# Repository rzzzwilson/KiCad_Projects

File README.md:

# KiCad_Projects
A place for my KiCad designs.

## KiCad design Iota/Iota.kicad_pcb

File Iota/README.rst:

What is this?
=============

*Iota* is a minimal arduino-like clone of the
`Teensy 2.0 <https://www.pjrc.com/store/teensy.html>`_.
It is designed to be pin compatible with the Teensy without some of its features,
particularly:

* 5Volt circuit only
* mostly the same pinout as the Teensy

The aim is to not just get a working Teensy 2 clone, but to ensure that my
knowledge of how to build something like a Teensy is adequate.  Later the
Iota design will be embedded in designs such as the Headless VFO, a version
of DigitalVFO without the display and rotary encoder.

Design Documents
----------------

The *Misc* directory contains various documents:

* teensy_2.gif - the Teensy 2 schematic
* Teensy_2.0_pinout.png - the Teensy 2 pinout

The design of the *Iota* will start with the teensy_2.gif schematic.

Status
------

The 1.0 version was a bust.  The micro USB SMD mount components I ordered don't
match the component footprint I used on the PCB.  There's no way to bodge the
SMD components to fit the board, so onto version 1.1.

2019_04_03: The 1.1 board using an SMD mini B USB socket has arrived.  After
fiddling with the crystal loading capacitors (increased to 22pF) and burning a
bootloader into the CPU, IT WORKS!   Here's a picture of it running the Adafruit
GFX library demo using an little 128x64 OLED display from AliExpress:

.. image:: IMG_5709.JPG

Burning the bootloader
----------------------

I followed this procedure to
`bootload the AtMega32U4 <https://murchlabs.com/monday-experiment-bootloading-an-atmega32u4-with-arduino/>`_.

The procedure (cleaned up) is:

1. Attach Uno to PC
2. Load sketch from File|Sketch|11.Arduino Isp|ArduinoISP
3. Disconnect Uno from PC
4. Connect the Iota to the Uno:
  * 10uF electro between GND and RESET on Uno
  * Vcc and GND on Uno to Iota
  * Uno 13 to Iota B1
  * Uno 12 to Iota B3
  * Uno 11 to Iota B2
  * Uno 10 to Iota RESET
5. Attach Uno to PC
6. Choose "Arduino Leonardo" from list of target boards
7. Burn the bootloader

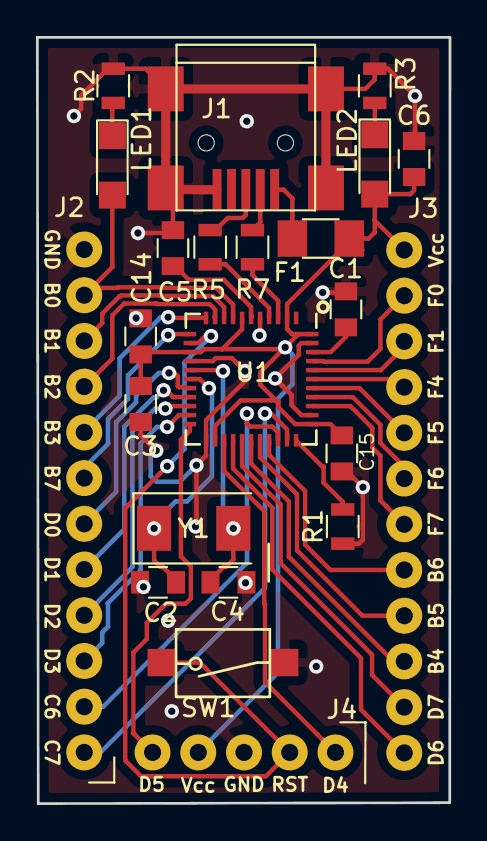
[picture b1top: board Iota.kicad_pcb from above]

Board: 2 copper layers, 22.9 x 42.6 mm, 24 parts (1 on the bottom side), 39 nets.

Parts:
C1, C3, C14, C15: 0.1uF; C_0805
C2, C4: 22pF; C_0805
C5, C6: 1uF; C_0805
F1: 500mA; Fuse_SMD1206_Wave
G1: LOGO; hanko
J1: USB_B_Mini; USB_Mini-B
J2, J3: Conn_01x12_Male; SL-112-X-XX_1x12
J4: Conn_01x05_Male; SL-105-X-XX_1x05
LED1: red; LED_1206
LED2: green; LED_1206
R1, R2, R3: 1K0; R_0805
R5, R7: 22; R_0805
SW1: SW_DIP_x01; Switch
U1: ATmega32U4-MU; QFN-44-1EP_7x7mm_Pitch0.5mm
Y1: 16MHz; Crystal_SMD_0603-2pin_6.0x3.5mm

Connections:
B0: J2.11, LED1.2, U1.8
B1: J2.10, U1.9
B2: J2.9, U1.10
B3: J2.8, U1.11
B4: J3.10, U1.28
B5: J3.9, U1.29
B6: J3.8, U1.30
B7: J2.7, U1.12
C6: J2.2, U1.31
C7: J2.1, U1.32
D0: J2.6, U1.18
D1: J2.5, U1.19
D2: J2.4, U1.20
D3: J2.3, U1.21
D4: J4.1, U1.25
D5: J4.5, U1.22
D6: J3.12, U1.26
D7: J3.11, U1.27
D+: R5.1, U1.4
D-: R7.1, U1.3
F0: J3.2, U1.41
F1: J3.3, U1.40
F4: J3.4, U1.39
F5: J3.5, U1.38
F6: J3.6, U1.37
F7: J3.7, U1.36
GND: C1.1, C2.2, C3.1, C4.2, C5.1, C6.1, C14.1, C15.1, J1.5, J1.6, J2.12, J4.3, R1.1, R2.2, R3.2, SW1.2, U1.5, U1.15, U1.23, U1.35, U1.43
unnamed: C1.2, U1.42
unnamed: C2.1, U1.17, Y1.1
unnamed: C4.1, U1.16, Y1.2
unnamed: C5.2, U1.6
unnamed: F1.2, J1.1
unnamed: J1.2, R7.2
unnamed: J1.3, R5.2
unnamed: LED1.1, R2.1
unnamed: LED2.1, R3.1
unnamed: R1.2, U1.33
RESET: J4.2, SW1.1, U1.13
Vcc: C3.2, C6.2, C14.2, C15.2, F1.1, J3.1, J4.4, LED2.2, U1.2, U1.7, U1.14, U1.24, U1.34, U1.44

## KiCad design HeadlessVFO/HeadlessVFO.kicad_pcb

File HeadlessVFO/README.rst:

What is this?
=============

*HeadlessVFO* is a near-clone of the
`DDS-60 <http://midnightdesignsolutions.com/dds60/>`_
from `Midnight Design Solutions <http://midnightdesignsolutions.com/>`_
with an embedded microcontroller.  The aim is to produce a black box like
the DigitalVFO project but without the display and rotary encoder.

The features desired are::

* RF output, 2 volts peak-to-peak, with a frequency between 1 and 60 MHz
* Powered from the USB connection
* Controlled by an external computer via the USB connection

Design Documents
----------------

The *Misc* directory contains various documents:

* DDS-60_Schematic_A5.pdf - the DDS-60 schematic from Midnight Design Solutions
* Iota_schematic.pdf - the Iota schematic, the brains of HeadlessVFO

Status
------

Currently working on the schematic.  The VFO part is mostly done.

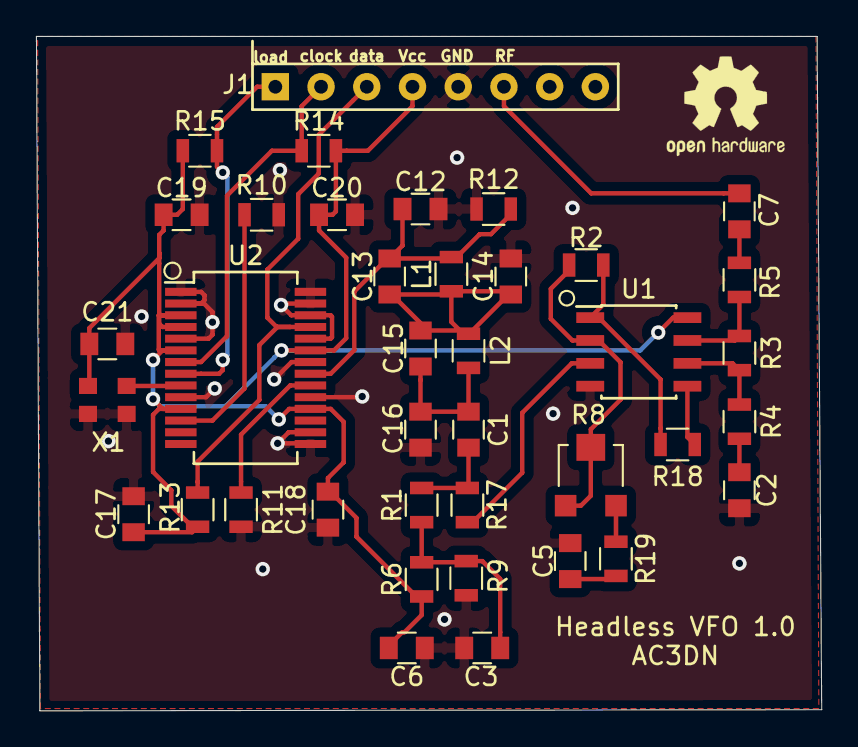
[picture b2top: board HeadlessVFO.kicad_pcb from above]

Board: 2 copper layers, 43.6 x 37.5 mm, 39 parts (0 on the bottom side), 24 nets.

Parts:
C1, C2, C3, C5, C7, C17, C18, C19, C20, C21: 0.1; C_0805
C6: 0.22; C_0805
C12: 47; C_0805
C13, C15: 15; C_0805
C14: 100; C_0805
C16: 82; C_0805
J1: Header_8x1
L1, L2: 0.1uH; L_0805
R1, R5: 51; R_0805
R2: 560; R_0805
R3: 620; R_0805
R4, R17, R18: 200; R_0805
R6, R9: 1K0; R_0805
R8: 500; Potentiometer_Trimmer-EVM3E
R10: 5K6; R_0805
R11, R19: 24R; R_0805
R12: 51R; R_0805
R13, R14, R15: 10K; R_0805
U1: AD8008; SOIC-8_3.9x4.9mm_Pitch1.27mm
U2: AD9851; SSOP-28_5.3x10.2mm_Pitch0.65mm
X1: TCXO; Oscillator_SMD_EuroQuartz_XO32-4pin_3.2x2.5mm

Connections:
CLOCK: J1.2, R14.1, U2.7
DATA: J1.3, R13.1, U2.25
GND: C2.2, C3.2, C5.2, C6.2, C12.2, C14.2, C16.2, C17.2, C18.2, C19.2, C20.2, C21.1, J1.5, R9.2, R10.2, R11.1, R12.1, U1.4, U2.1, U2.2, U2.5, U2.10, U2.15, U2.16, U2.19, U2.22, U2.24, U2.26, U2.27, U2.28, X1.1, X1.2
LOAD: J1.1, R15.1, U2.8
unnamed: C1.1, R1.2, R17.1
unnamed: C1.2, C15.1, C16.1, L2.1
unnamed: C2.1, R4.1
unnamed: C3.1, R1.1, R6.2, R9.1
unnamed: C5.1, R19.1
unnamed: C7.2, R5.2
unnamed: C12.1, C13.2, L1.2, R12.2, U2.21
unnamed: C13.1, C14.1, C15.2, L1.1, L2.2
unnamed: R2.1, R8.1, R8.2, U1.2
unnamed: R3.1, R4.2, U1.6
unnamed: R3.2, R5.1, U1.7
unnamed: R10.1, U2.12
unnamed: R11.2, U2.20
unnamed: R17.2, U1.3
unnamed: R2.2, R18.1, U1.1
unnamed: R18.2, U1.5
unnamed: R8.3, R19.2
unnamed: U2.9, X1.3
RFout: C7.1, J1.6
Vcc: C6.1, C17.1, C18.1, C19.1, C20.1, C21.2, J1.4, R6.1, R13.2, R14.2, R15.2, U1.8, U2.3, U2.4, U2.6, U2.11, U2.18, U2.23, X1.4

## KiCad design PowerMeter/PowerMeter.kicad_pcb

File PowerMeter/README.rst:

This is a small PCB used to build the main circuit of the design
in "Simple RF-Power Measurement", an article from the June 2001
issue of the QST magazine.  The
`PDF of the article <https://github.com/rzzzwilson/KiCad_Projects/blob/master/PowerMeter/docs/build%20an%20rf%20power%20meter.pdf>`_
is in the *docs* subdirectory.

23 April, 2019
--------------

Ready for production.  The schematic:

.. image:: Schematic.png

and the PCB:

.. image:: PCB.png

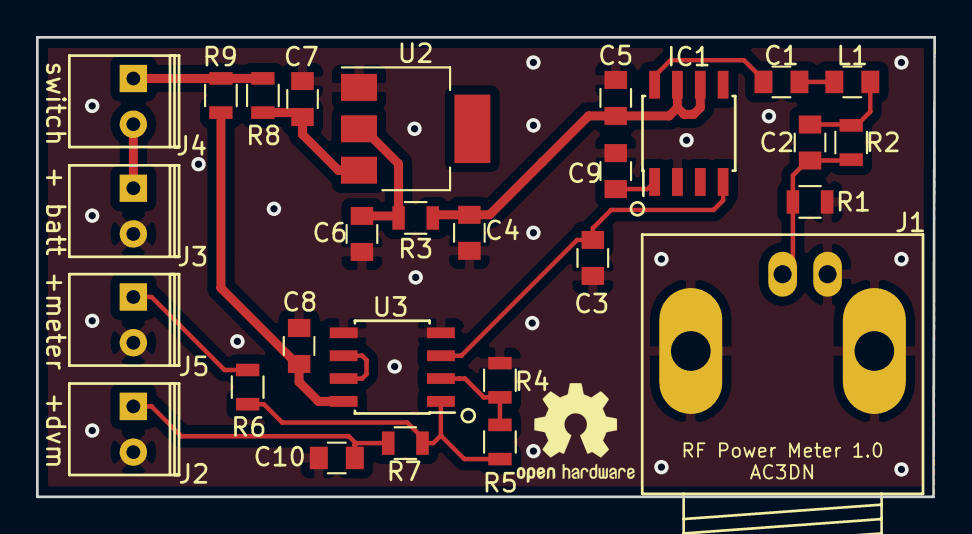
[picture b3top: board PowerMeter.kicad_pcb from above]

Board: 2 copper layers, 49.8 x 25.5 mm, 28 parts (0 on the bottom side), 18 nets.

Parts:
C1: 0.01uF; C_0805
C2: 15pF; C_0805
C3, C4, C5, C8, C9: 0.1uF; C_0805
C6, C7: 0.22uF; C_0805
C10: 0.001uF; C_0805
IC1: AD8307; SOIC-8_3.9x4.9mm_Pitch1.27mm
J1: RF Input; BNC_Socket_TYCO-AMP_LargePads
J2: DVM; Conn_1x2
J3: 9v Battery; Conn_1x2
J4: Switch; Conn_1x2
J5: 0-1 mA Meter; Conn_1x2
L1: *; C_0805
R1: 51; R_0805
R2: 470; R_0805
R3: 6R8; R_0805
R4: 3.3K; R_0805
R5: 4.7K; R_0805
R6: 6.8K; R_0805
R7: 10K; R_0805
R8: 6K8; R_0805
R9: 51R; R_0805
U2: LM1117-5.0; SOT-223
U3: LM358; SOIC-8_3.9x4.9mm_Pitch1.27mm

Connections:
+5V: C6.2, R3.1, U2.2
+BATT: J4.1, R8.1, R9.2
GND: C3.1, C4.1, C5.1, C6.1, C7.1, C8.1, C9.1, C10.1, IC1.2, J1.2, J2.2, J3.2, J5.2, R1.1, R4.2, U2.1, U3.4, U3.5
unnamed: C1.1, IC1.8
unnamed: C1.2, L1.2
unnamed: C2.1, L1.1, R2.1
unnamed: C2.2, J1.1, R1.2, R2.2
unnamed: C3.2, IC1.4, U3.3
unnamed: C4.2, C5.2, IC1.6, IC1.7, R3.2
unnamed: C7.2, R8.2, U2.3
unnamed: C8.2, R9.1, U3.8
unnamed: C9.2, IC1.1
unnamed: C10.2, J2.1, R7.1
unnamed: J3.1, J4.2
unnamed: J5.1, R6.1
unnamed: R4.1, R5.2, U3.2
unnamed: R5.1, R6.2, R7.2, U3.1
unnamed: U3.6, U3.7

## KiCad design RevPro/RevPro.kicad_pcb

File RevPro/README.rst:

This is a simple circuit to provide reverse polarity protection to any circuit
I build.  The idea came from
`NoGSG via the ARRL <http://www.arrl.org/files/file/Technology/HandsOnRadio/Thoughts%20on%20Reverse%20Power%20Protection%20using%20Power%20MOSFETs%20-%20Wheeler%20N0GSG.pdf>`_
and the SuperCon presentation by
`Chris Gammel <https://www.youtube.com/watch?v=TsrRr4Iq6_M>`_.

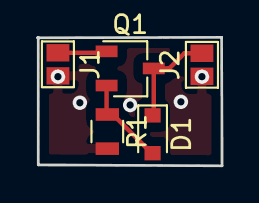
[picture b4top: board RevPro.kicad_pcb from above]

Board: 2 copper layers, 10.3 x 7.1 mm, 5 parts (0 on the bottom side), 4 nets.

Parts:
D1: 10V; D_0805
J1: Input; GS2
J2: Output; GS2
Q1: AO3401; TSOT-23
R1: 100K; R_0805

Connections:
GND: J1.2, J2.1, R1.2
unnamed: D1.1, J2.2, Q1.3
unnamed: D1.2, Q1.2, R1.1
unnamed: J1.1, Q1.1

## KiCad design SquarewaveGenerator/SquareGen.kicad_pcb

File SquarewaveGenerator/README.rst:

SquareGen
=========

This project is a repackaging of the fast risetime Square Wave generator
that I built from the 
`video by W2AEW on YouTube <https://www.youtube.com/watch?v=9cP6w2odGUc>`_.
I originally put this circuit into an enclosure using the "dead bug" style
and it worked pretty well.  Here's the built circuit:

.. image:: IMG_5211.JPG

And here's the circuit running on the 'scope:

.. image:: DS1Z_QuickPrint3.png

Not bad for a cheap little circuit.  This shows a risetime of 2.7 nanoseconds.
The ringing has a frequency of about 130MHz.  Here the generator is working
into a 50Ω load and the peak-to-peak voltage is just over 2.5v.
It draws just under 30mA.

I have been building circuits on PCB lately using the PCB shops in China with
through-hole components, but now I want to get into surface-mounted components
so I'm using this circuit as a guinea-pig.  Using KiCAD here's the schematic:

.. image:: schematic.png

and the PCB itself:

.. image:: pcb.png

I'll put the PCB into the same 25x25x50mm enclosure as the first circuit, so the
PCB measures about 44x23mm.  I got the enclosures 
`from here <https://www.aliexpress.com/wholesale?catId=0&initiative_id=SB_20180825211723&SearchText=50x25x25mm+Extruded+Aluminum>`_.

18 October 2018
===============

The SMD PCB is back from China and the circuit has been built.  Here is the
assembled board being tested:

.. image:: IMG_5367.JPG

and the board installed in a small 25x25x50mm case:

.. image:: IMG_5427.JPG

With the generator working into a 50 ohm load it draws about 30mA at 5v.  Here's
a close look at the leading edge of the 3KHz square wave.  Risetime is even
better than the first version at 1.7ns.  Not shown is a 700KHz low frequency
ringing.

.. image:: DS1Z_QuickPrint5.png

Next version
============

The SMD version above works very well, but there are a few things that could be
improved, such as:

* thicker connections on the output side,
* 50 ohm connections to the output pad,
* better power/RF connection pads,
* use a groundplane on the back side of the board.

The board is sized to fit into the 25x25x50mm case *diagonally* which will allow
much shorter connections for power and signal.  Here's the PCB:

.. image:: Version3PCB.png

4 December 2018
===============

The PCB shown above has arrived and has been built.  Performance is slightly
better than the previous version.  Everything else is about the same, but the
leading edge risetime is now 1.6ns.

.. image:: DS1Z_QuickPrint4.png

The only improvement I want to try is to add a 10uF decoupling capacitor to
the power input trace.  Testing it out by patching the board saw no change apart
from removing the 700KHz low frequency ringing.  Still, it's worth doing and
the latest KiCad design includes the capacitor.  I won't make a PCB for this
as the patched version works fine.  The final PCB looks like this:

.. image:: Version3.1PCB.png

Here's a shot of the "patched" board in its case:

.. image:: IMG_6316.JPG

That's about as far I will go with this simple circuit.

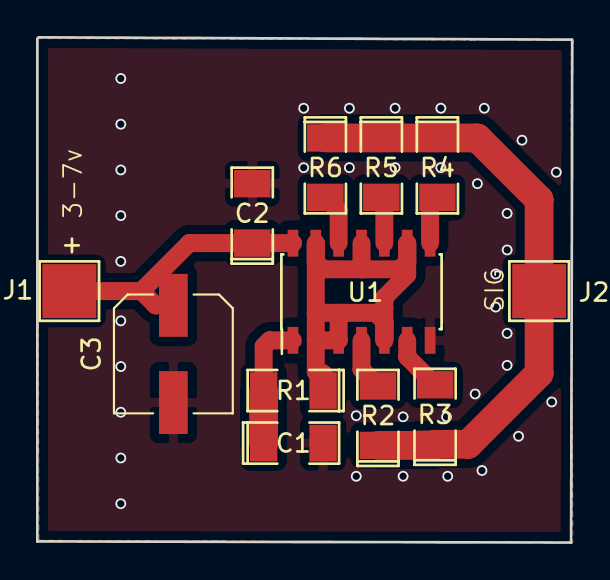
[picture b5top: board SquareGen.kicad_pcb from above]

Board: 2 copper layers, 29.7 x 28.1 mm, 12 parts (0 on the bottom side), 10 nets.

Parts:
C1: 47nF; SMD-1206_Pol
C2: 100nF; SMD-1206_Pol
C3: 10uF; CP_Elec_6.3x5.7
J1, J2: Power_RF_Pads
R1: 6.8K; SMD-1206_Pol
R2, R3, R4, R5, R6: 220; SMD-1206_Pol
U1: 74AC14; SOIC-14_3.9x8.7mm_Pitch1.27mm

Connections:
GND: C1.2, C2.2, C3.2, J1.2, J2.2, U1.7
unnamed: C1.1, R1.2, U1.1
unnamed: J2.1, R2.1, R3.1, R4.1, R5.1, R6.1
unnamed: R1.1, U1.2, U1.3, U1.5, U1.9, U1.11, U1.13
unnamed: R2.2, U1.4
unnamed: R3.2, U1.6
unnamed: R4.2, U1.8
unnamed: R5.2, U1.10
unnamed: R6.2, U1.12
VCC: C2.1, C3.1, J1.1, U1.14

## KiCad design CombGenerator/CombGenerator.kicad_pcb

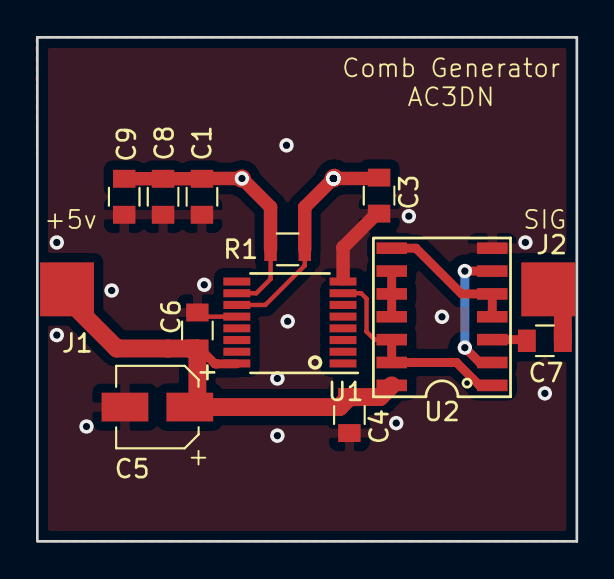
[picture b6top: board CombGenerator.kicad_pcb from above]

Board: 2 copper layers, 30.0 x 28.0 mm, 14 parts (0 on the bottom side), 10 nets.

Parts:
C1: 180pF; C_0805
C3: 220pF; C_0805
C4, C6, C7: 47nF; C_0805
C5: 3.3uF; CP_Elec_4x5.8
C8, C9: 22pF; C_0805
J1: Barrel_Jack; Pad_Power_RF
J2: Conn_Coaxial; Pad_Power_RF
R1: 1M; R_0805
U1: 4060; TSSOP-16_4.4x5mm_Pitch0.65mm
U2: 7400; 74AC00
Y1: 400KHz; Resonator

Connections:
/Vcc: C4.1, C5.1, C6.1, J1.1, U1.16, U2.14
GND: C1.2, C3.2, C4.2, C5.2, C6.2, C8.2, C9.2, J1.2, J2.2, U1.8, U1.12, U2.7
unnamed: C1.1, C8.1, C9.1, R1.2, U1.10, Y1.2
unnamed: C3.1, R1.1, U1.11, Y1.1
unnamed: C7.1, J2.1
unnamed: C7.2, U2.3
unnamed: U1.7, U2.1, U2.12, U2.13
unnamed: U2.2, U2.6
unnamed: U2.4, U2.5, U2.8
unnamed: U2.9, U2.10, U2.11

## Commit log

2018-11-21 Added README.rst
2018-11-21 Ignore generated 'gerber' directories
2018-11-21 Added other projects
2018-11-23 PCB design that was submitted
2018-11-29 Leave DigitalVFO as a solo repository
2018-11-30 Removed empty directories
2018-11-30 Added square wave generator
2018-11-30 Removed DigitalVFO
2018-12-01 Updated SMD scope photo
2018-12-04 Final update of this project.
2018-12-04 Slight touchup of README
2018-12-05 Added 10uF power decoupling
2018-12-12 Added missing power+ground connections
2018-12-12 Added Iota and TestCrystalOscillator
2019-01-22 Build picture
2019-01-22 Better doc
2019-01-22 Fix minor blemish
2019-01-22 Added power circuit
2019-01-23 Updated schematic
2019-01-26 Update README and Misc files
2019-01-27 Starting PCB design
2019-01-28 Working on PCB layout
2019-01-31 Still faffing around laying out tracks
2019-02-06 Still fiddling with PCB layout
2019-02-06 Move to Teensy 2.0 clone
2019-02-07 Teensy 2 documentation
2019-02-07 Added switch footprint
2019-02-07 Switch over to Teensy 2 clone
2019-02-07 Update README with Teensy data
2019-02-08 Finalizing PCB layout
2019-02-10 Checking traces, footprint sizing
2019-02-11 Adding in F+B silkscreen markings
2019-02-14 My hanko logo
2019-02-14 Cleaned up and submitted to Seeed
2019-02-17 Started the 'Reverse Polarity' project
2019-02-26 Update for the 1.1 board
2019-03-11 Minor changes
2019-03-11 Update project status
2019-04-03 Finalizing
2019-04-04 Added power LED
2019-04-04 Bumped version to 1.2
2019-04-04 Updated schematic PDF
2019-04-08 Adding the Power Meter
2019-04-08 Update the README
2019-04-08 Need this file in git?
2019-04-08 Add the AtMega32U4 breakout board
2019-04-15 Updated status
2019-04-23 Added footprints
2019-04-23 Minor changes preparing for production
2019-04-23 Added logo
2019-04-23 Added schematic and PCB pic
2019-04-23 Updated README status
2019-06-01 Starting schematic
2019-06-02 Finished the VFO part
2019-06-02 Update status
2019-06-08 Starting the PCB
2019-06-12 Almost finished PCB
2019-06-18 Changed R8 to 6.8K
2019-06-18 Final changes before making board
2019-06-18 Schematic was right, undo previous change
2019-06-24 Update to QFN44 chip
2019-06-25 Fixed funny PDF name
2019-06-25 Gerbers for v1.1
2019-06-25 Board layout is clean
2019-06-26 Ready for PCB fabrication
2019-06-26 Don't ignore output gerber *.zip
2019-06-26 Save production ZIP files
2019-07-12 Final for 1.2
2019-07-12 Ignore the drill files
2020-02-18 Added final picture.
2020-07-14 Small change
2020-09-16 Revert "Gerbers for v1.1"
    This reverts commit 79ea9522353ad99a5974402a4ced439cf9111e6b.
2020-09-16 Revert "Fixed funny PDF name"
    This reverts commit 46ce3cb9b1fc1f6b2d386a8ecacbb81f4989a39a.
2020-09-16 Changes???
2020-09-16 Add something to do with KiCad
2020-09-16 Blink without delay for Iota
